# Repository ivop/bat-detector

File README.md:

# BAT DETECTOR

Detect bats - frequency divider  
  
based on [Bat-Detector instructable](https://www.instructables.com/Bat-Detector/)

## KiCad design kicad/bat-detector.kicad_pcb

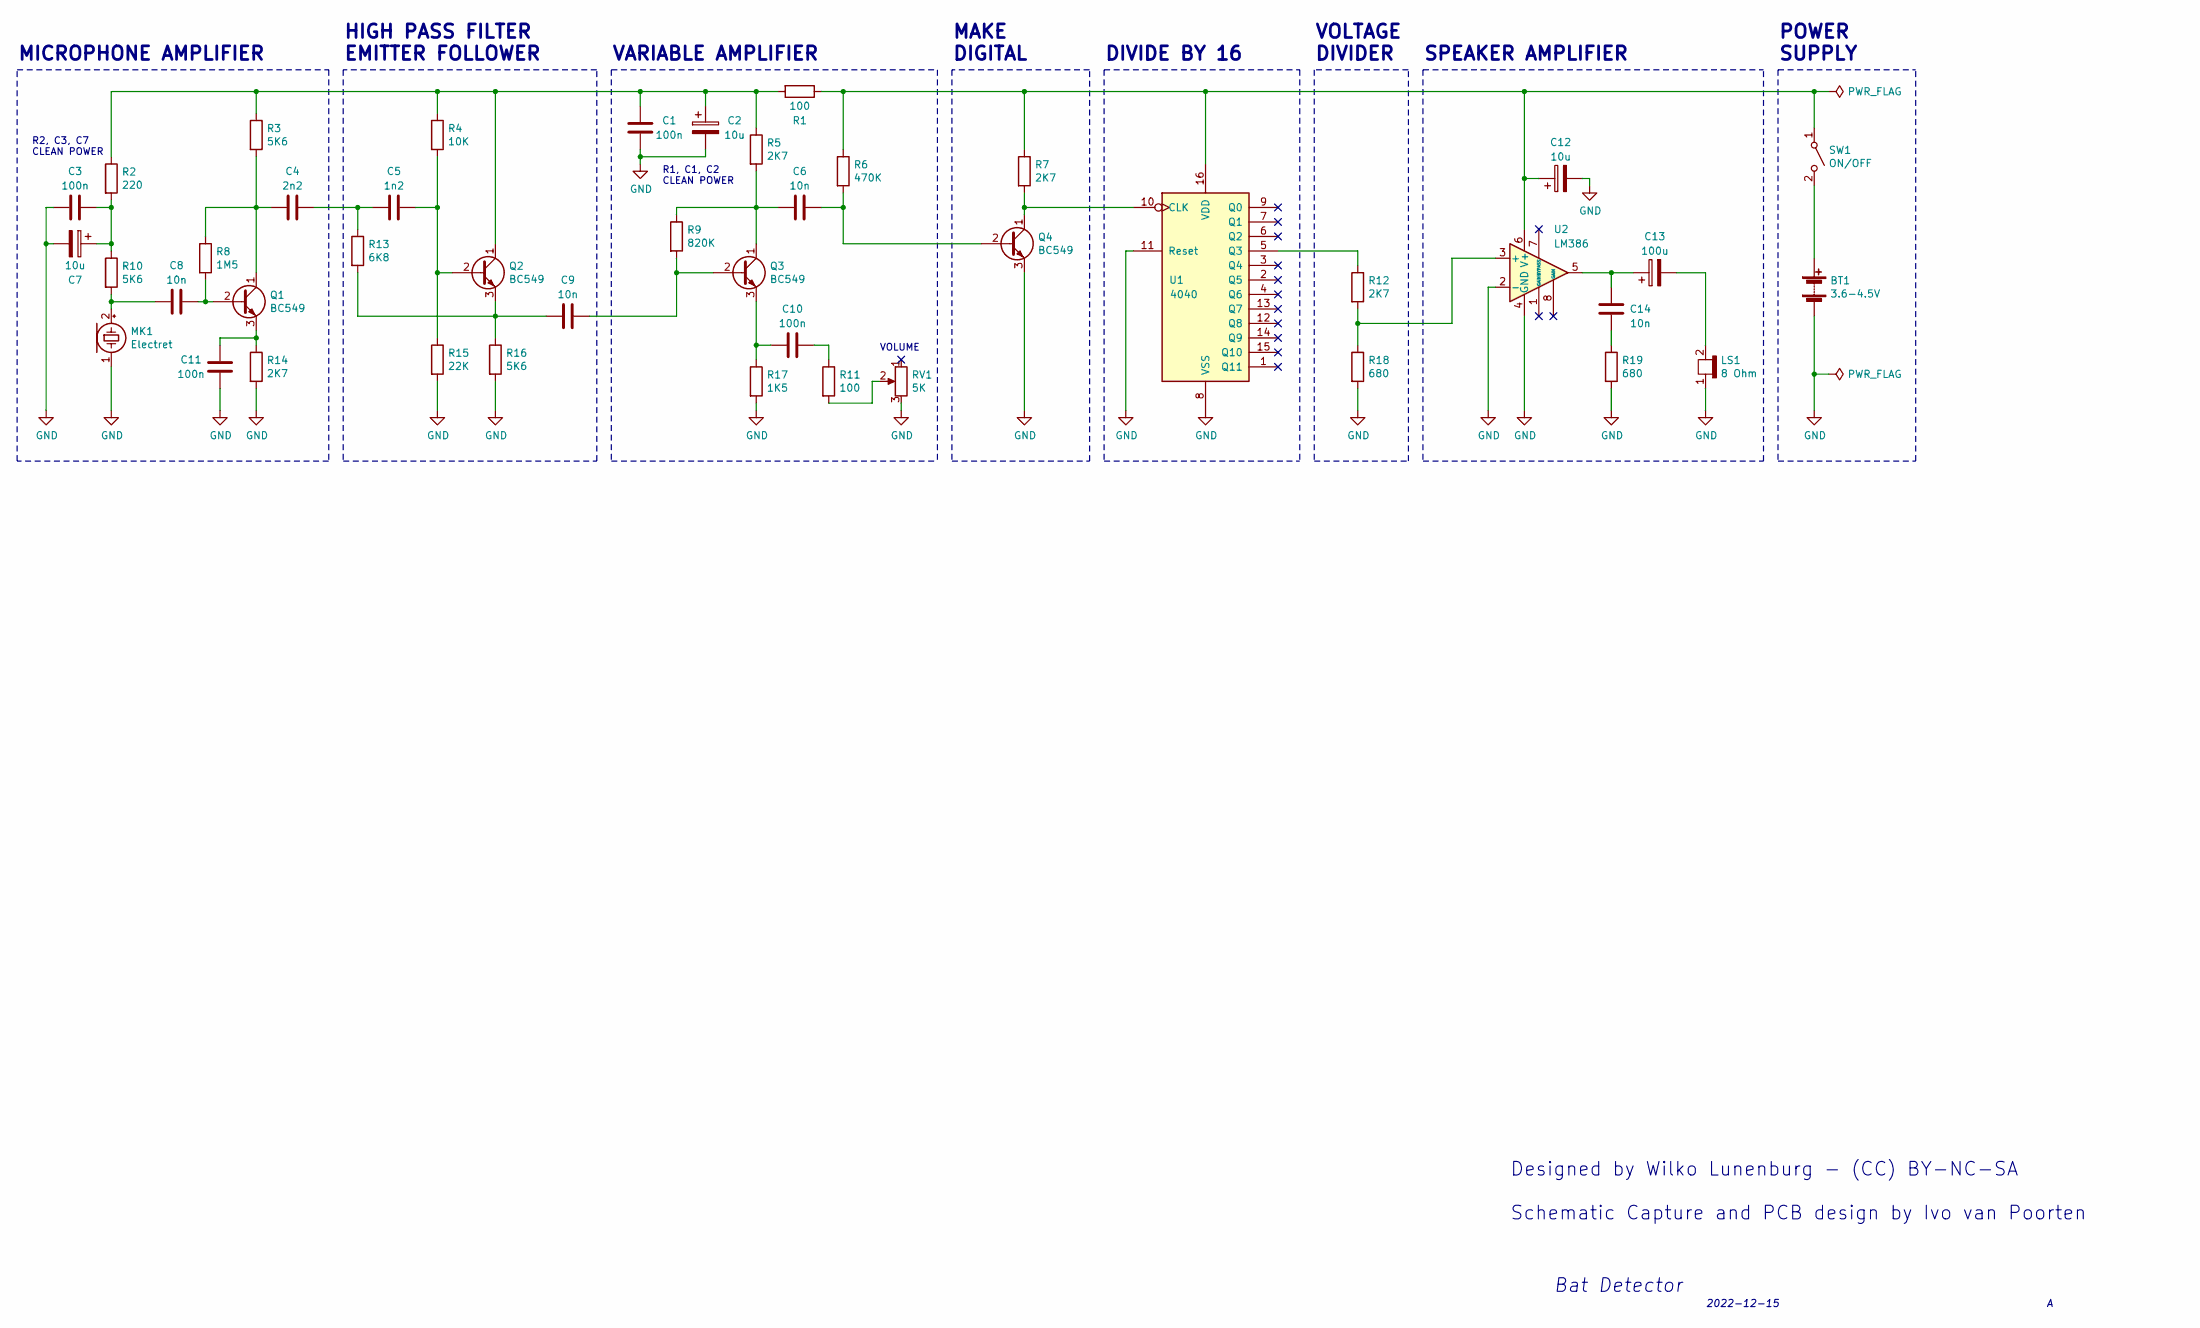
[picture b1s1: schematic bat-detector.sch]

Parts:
BT1: 3.6-4.5V; PinHeader_1x02_P2.54mm_Vertical
C1, C3, C10, C11: 100n; C_Disc_D5.0mm_W2.5mm_P2.50mm
C2, C7, C12: 10u; CP_Radial_D5.0mm_P2.50mm
C4: 2n2; C_Disc_D5.0mm_W2.5mm_P2.50mm
C5: 1n2; C_Disc_D5.0mm_W2.5mm_P2.50mm
C6, C8, C9, C14: 10n; C_Disc_D5.0mm_W2.5mm_P2.50mm
C13: 100u; CP_Radial_D7.5mm_P2.50mm
LS1: 8 Ohm; PinHeader_1x02_P2.54mm_Vertical
MK1: Electret; PinHeader_1x02_P2.54mm_Vertical
Q1, Q2, Q3, Q4: BC549; TO-92_Inline
R1, R11: 100; R_Axial_DIN0204_L3.6mm_D1.6mm_P7.62mm_Horizontal
R2: 220; R_Axial_DIN0204_L3.6mm_D1.6mm_P7.62mm_Horizontal
R3, R10, R16: 5K6; R_Axial_DIN0204_L3.6mm_D1.6mm_P7.62mm_Horizontal
R4: 10K; R_Axial_DIN0204_L3.6mm_D1.6mm_P7.62mm_Horizontal
R5, R7, R12, R14: 2K7; R_Axial_DIN0204_L3.6mm_D1.6mm_P7.62mm_Horizontal
R6: 470K; R_Axial_DIN0204_L3.6mm_D1.6mm_P7.62mm_Horizontal
R8: 1M5; R_Axial_DIN0204_L3.6mm_D1.6mm_P7.62mm_Horizontal
R9: 820K; R_Axial_DIN0204_L3.6mm_D1.6mm_P7.62mm_Horizontal
R13: 6K8; R_Axial_DIN0204_L3.6mm_D1.6mm_P7.62mm_Horizontal
R15: 22K; R_Axial_DIN0204_L3.6mm_D1.6mm_P7.62mm_Horizontal
R17: 1K5; R_Axial_DIN0204_L3.6mm_D1.6mm_P7.62mm_Horizontal
R18, R19: 680; R_Axial_DIN0204_L3.6mm_D1.6mm_P7.62mm_Horizontal
RV1: 5K; PinHeader_1x03_P2.54mm_Vertical
SW1: ON/OFF; PinHeader_1x02_P2.54mm_Vertical
U1: 4040; DIP-16_W7.62mm_Socket_LongPads
U2: LM386; DIP-8_W7.62mm_Socket_LongPads

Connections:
GND: BT1.2 (-), C1.1, C2.2, C3.2, C7.2, C11.2, C12.2, LS1.1 (-), MK1.1 (-), Q4.3 (E), R14.2, R15.2, R16.2, R17.2, R18.2, R19.2, RV1.3, U1.8 (VSS), U1.11 (Reset), U2.2 (-), U2.4 (GND); also elsewhere on the board
unnamed: BT1.1 (+), SW1.2 (B)
unnamed: C1.2, C2.1, Q2.1 (C), R1.2, R2.1, R3.1, R4.1, R5.1
unnamed: C3.1, C7.1, R2.2, R10.1
unnamed: C4.1, C5.2, R13.1
unnamed: C4.2, Q1.1 (C), R3.2, R8.1
unnamed: C5.1, Q2.2 (B), R4.2, R15.1
unnamed: C6.1, Q4.2 (B), R6.2
unnamed: C6.2, Q3.1 (C), R5.2, R9.1
unnamed: C8.1, Q1.2 (B), R8.2
unnamed 10: C8.2, MK1.2 (+), R10.2; also elsewhere on the board
unnamed: C9.1, Q3.2 (B), R9.2
unnamed: C9.2, Q2.3 (E), R13.2, R16.1
unnamed: C10.1, R11.1
unnamed: C10.2, Q3.3 (E), R17.1
unnamed: C11.1, Q1.3 (E), R14.1
unnamed: C12.1, R1.1, R6.1, R7.1, SW1.1 (A), U1.16 (VDD), U2.6 (V+)
unnamed: C13.1, C14.2, U2.5
unnamed: C13.2, LS1.2 (+)
unnamed: C14.1, R19.1
unnamed: Q4.1 (C), R7.2, U1.10 (CLK)
unnamed: R11.2, RV1.2
unnamed: R12.1, U1.5 (Q3)
unnamed: R12.2, R18.1, U2.3 (+)

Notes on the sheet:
R2, C3, C7 CLEAN POWER
R1, C1, C2 CLEAN POWER
VOLUME
MAKE DIGITAL
DIVIDE BY 16
VOLTAGE DIVIDER
SPEAKER AMPLIFIER
POWER SUPPLY
Designed by Wilko Lunenburg - (CC) BY-NC-SA Schematic Capture and PCB design by Ivo van Poorten
Bat Detector
2022-12-15
VARIABLE AMPLIFIER
MICROPHONE AMPLIFIER
HIGH PASS FILTER EMITTER FOLLOWER

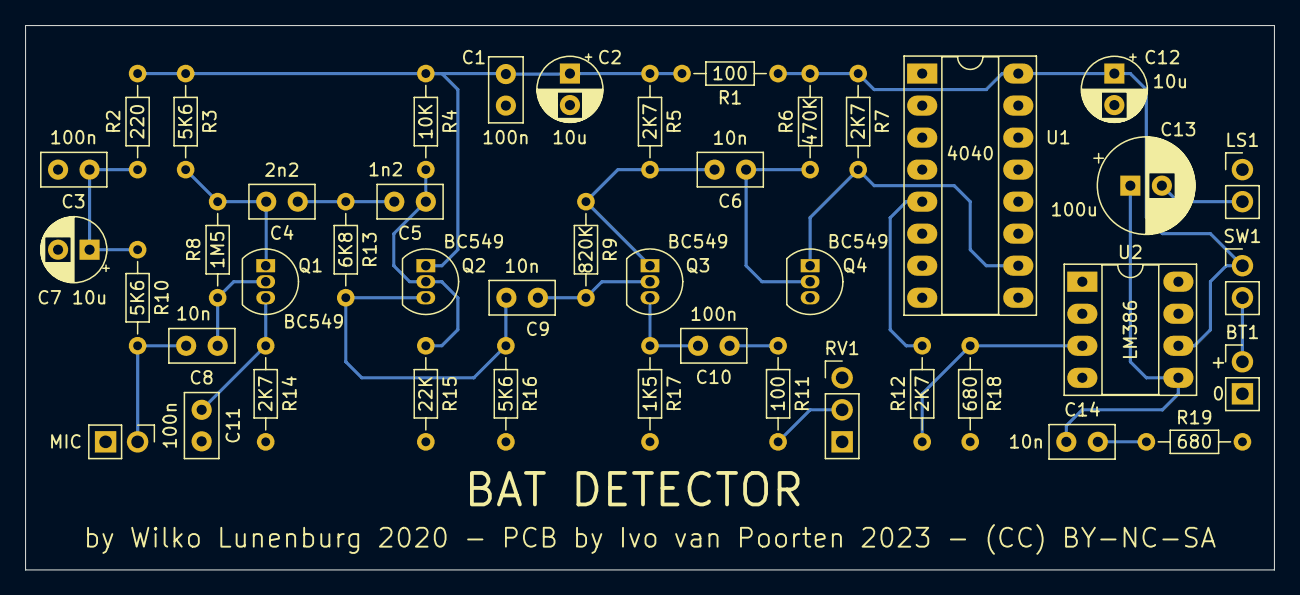
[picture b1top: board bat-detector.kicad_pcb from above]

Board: 2 copper layers, 99.1 x 43.2 mm, 44 parts (0 on the bottom side), 24 nets.

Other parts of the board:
MIC: Electret; PinHeader_1x02_P2.54mm_Vertical

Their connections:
GND: MIC.1; also elsewhere on the board
unnamed 10: MIC.2; also elsewhere on the board

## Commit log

2023-01-16 ignore backup files
2023-01-16 add kicad files and pdf of schematic
2023-01-16 short description and images
2023-01-16 fix images
2023-01-16 add images
2023-01-16 add gerbers
